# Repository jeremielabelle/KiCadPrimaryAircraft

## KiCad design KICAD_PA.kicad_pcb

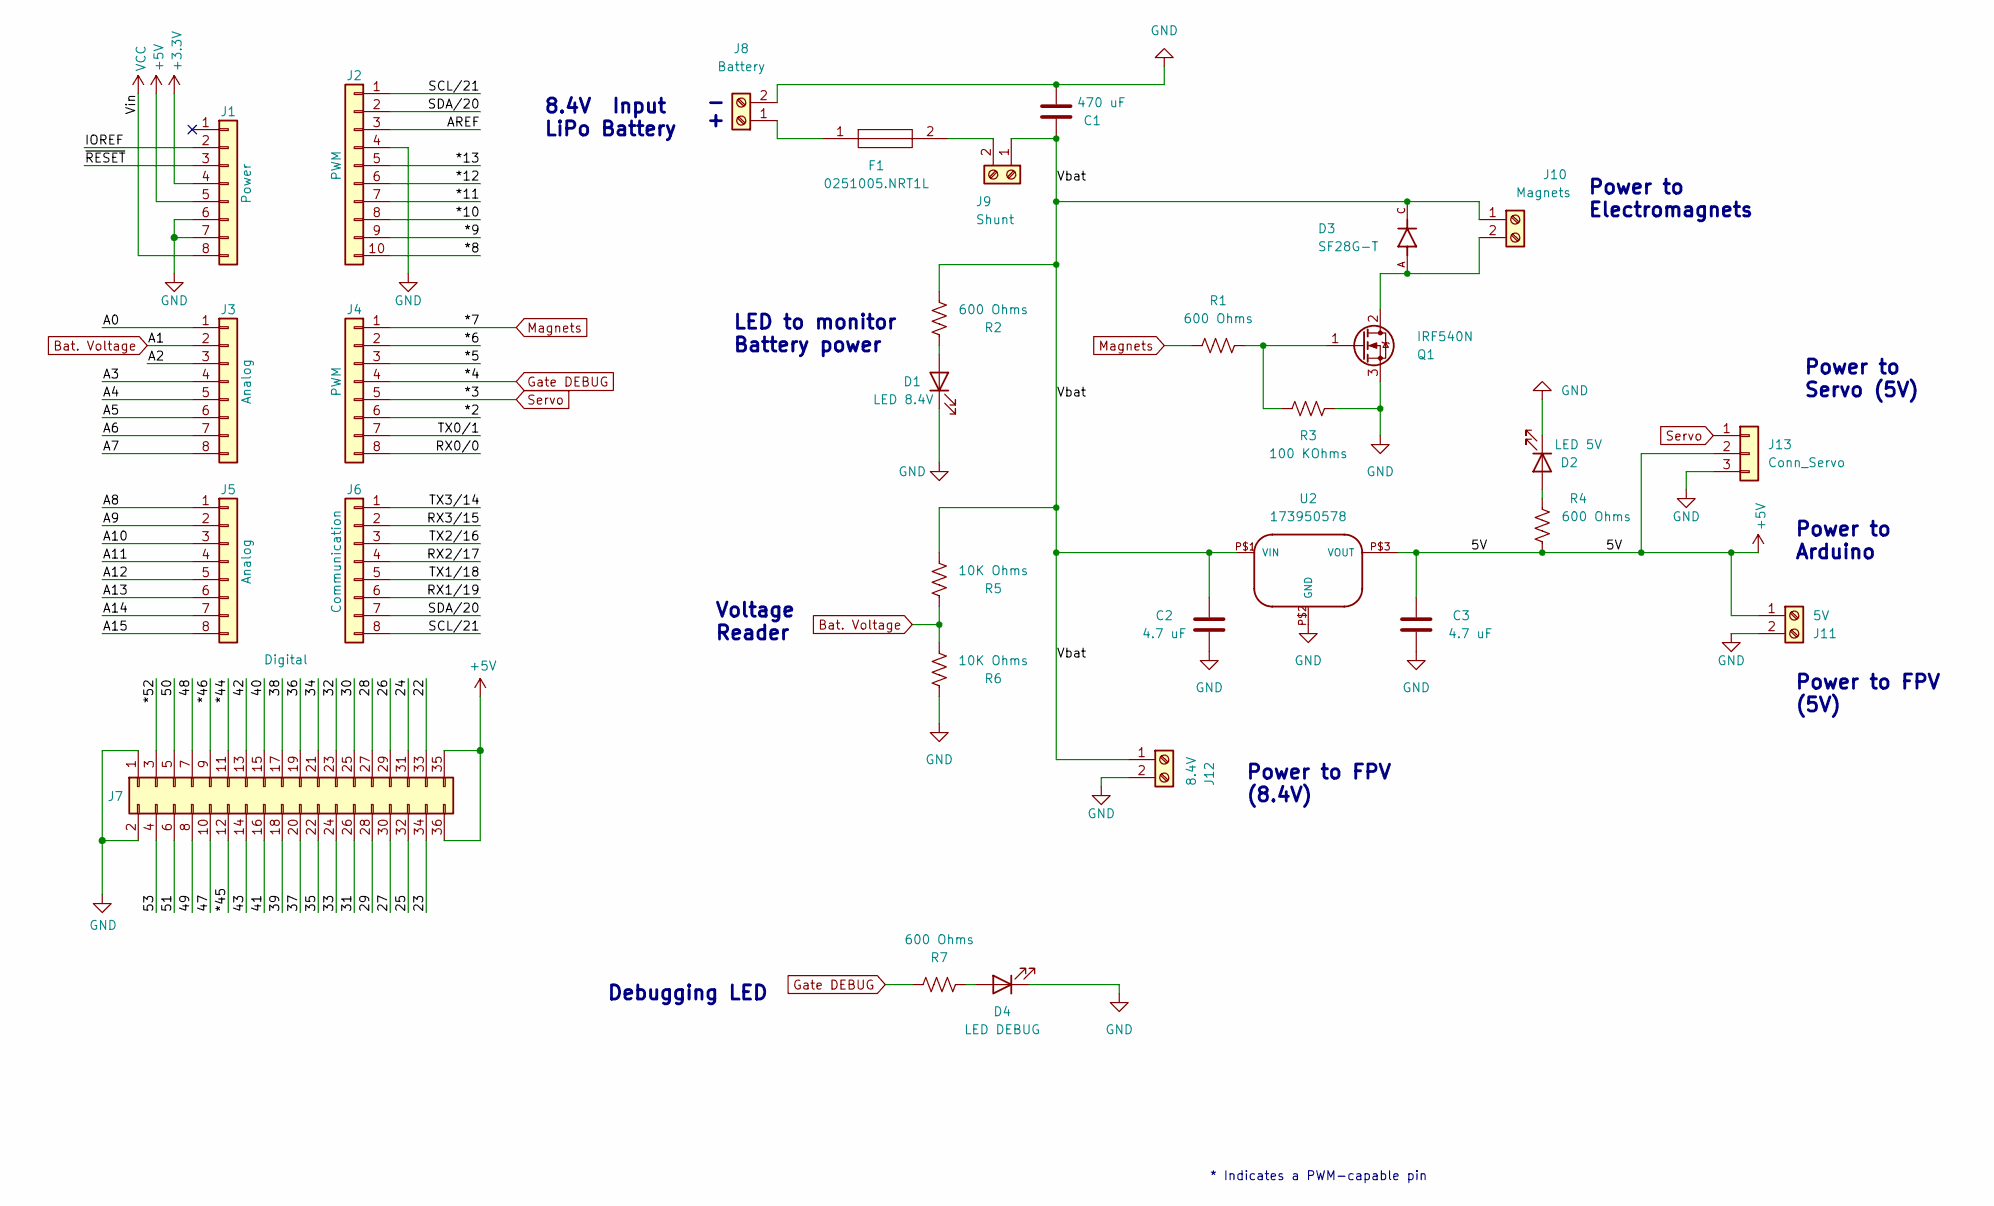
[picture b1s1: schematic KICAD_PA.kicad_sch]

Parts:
C1: 470 uF; CP_Radial_D12.5mm_P5.00mm
C2, C3: 4.7 uF; CP_Radial_D5.0mm_P2.00mm
D1: LED 8.4V; LED_D5.0mm_Horizontal_O3.81mm_Z3.0mm
D2: LED 5V; LED_D5.0mm_Horizontal_O3.81mm_Z3.0mm
D3: SF28G-T; DIOAD1300W80L670D310; PARTREV F2105
D4: LED DEBUG; LED_D5.0mm_Horizontal_O3.81mm_Z3.0mm
F1: 0251005.NRT1L; RESAD1831W64L711D280; Manufacturer_Part_Number 0251005.NRT1L; Mouser Part Number 576-0251005.NRT1L
J1: Power; PinSocket_1x08_P2.54mm_Vertical
J2: PWM; PinSocket_1x10_P2.54mm_Vertical
J3, J5: Analog; PinSocket_1x08_P2.54mm_Vertical
J4: PWM; PinSocket_1x08_P2.54mm_Vertical
J6: Communication; PinSocket_1x08_P2.54mm_Vertical
J7: Digital; PinSocket_2x18_P2.54mm_Vertical
J8: Battery; TerminalBlock_bornier-2_P5.08mm
J9: Shunt; TerminalBlock_bornier-2_P5.08mm
J10: Magnets; TerminalBlock_bornier-2_P5.08mm
J11: 5V; TerminalBlock_bornier-2_P5.08mm
J12: 8.4V; TerminalBlock_bornier-2_P5.08mm
J13: Conn_Servo; PinHeader_1x03_P2.54mm_Horizontal
Q1: IRF540N; TO-220-3_Vertical
R1, R2, R4, R7: 600 Ohms; R_Axial_DIN0207_L6.3mm_D2.5mm_P10.16mm_Horizontal
R3: 100 KOhms; R_Axial_DIN0516_L15.5mm_D5.0mm_P25.40mm_Horizontal
R5, R6: 10K Ohms; R_Axial_DIN0207_L6.3mm_D2.5mm_P10.16mm_Horizontal
U2: 173950578; SIP-3

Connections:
+3V3: J1.4
+5V: C3.1, J1.5, J7.35, J7.36, J11.1, J13.2, R4.2, U2.P$3 (VOUT)
/22: J7.33
/23: J7.34
/24: J7.31
/25: J7.32
/26: J7.29
/27: J7.30
/28: J7.27
/29: J7.28
/30: J7.25
/31: J7.26
/32: J7.23
/33: J7.24
/34: J7.21
/35: J7.22
/36: J7.19
/37: J7.20
/38: J7.17
/39: J7.18
/40: J7.15
/41: J7.16
/42: J7.13
/43: J7.14
/47: J7.10
/48: J7.7
/49: J7.8
/50: J7.5
/51: J7.6
/53: J7.4
/*2: J4.6
/*5: J4.3
/*6: J4.2
/*8: J2.10
/*9: J2.9
/*10: J2.8
/*11: J2.7
/*12: J2.6
/*13: J2.5
/*44: J7.11
/*45: J7.12
/*46: J7.9
/*52: J7.3
/A0: J3.1
/A2: J3.3
/A3: J3.4
/A4: J3.5
/A5: J3.6
/A6: J3.7
/A7: J3.8
/A8: J5.1
/A9: J5.2
/A10: J5.3
/A11: J5.4
/A12: J5.5
/A13: J5.6
/A14: J5.7
/A15: J5.8
/AREF: J2.3
/IOREF: J1.2
/RX0/0: J4.8
/RX1/19: J6.6
/RX2/17: J6.4
/RX3/15: J6.2
/SCL/21: J2.1, J6.8
/SDA/20: J2.2, J6.7
/TX0/1: J4.7
/TX1/18: J6.5
/TX2/16: J6.3
/TX3/14: J6.1
/Vbat: C1.1, C2.1, D3.C, J9.1, J10.1, J12.1, R2.2, R5.2, U2.P$1 (VIN)
/~RESET: J1.3
Bat. Voltage: J3.2, R5.1, R6.2
GND: C1.2, C2.2, C3.2, D1.1 (K), D2.1 (K), D4.1 (K), J1.6, J1.7, J2.4, J7.1, J7.2, J8.2, J11.2, J12.2, J13.3, Q1.3 (S), R3.1, R6.1, U2.P$2 (GND)
Gate DEBUG: J4.4, R7.2
Magnets: J4.1, R1.2
unnamed: D1.2 (A), R2.1
unnamed: D2.2 (A), R4.1
unnamed: D3.A, J10.2, Q1.2 (D)
unnamed: D4.2 (A), R7.1
unnamed: F1.1, J8.1
unnamed: F1.2, J9.2
unnamed: Q1.1 (G), R1.1, R3.2
Servo: J4.5, J13.1
VCC: J1.8

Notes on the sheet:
Power to Electromagnets
8.4V Input LiPo Battery
Power to Servo (5V)
Debugging LED
Power to Arduino
Power to FPV (8.4V)
Voltage Reader
* Indicates a PWM-capable pin
LED to monitor Battery power
Power to FPV (5V)

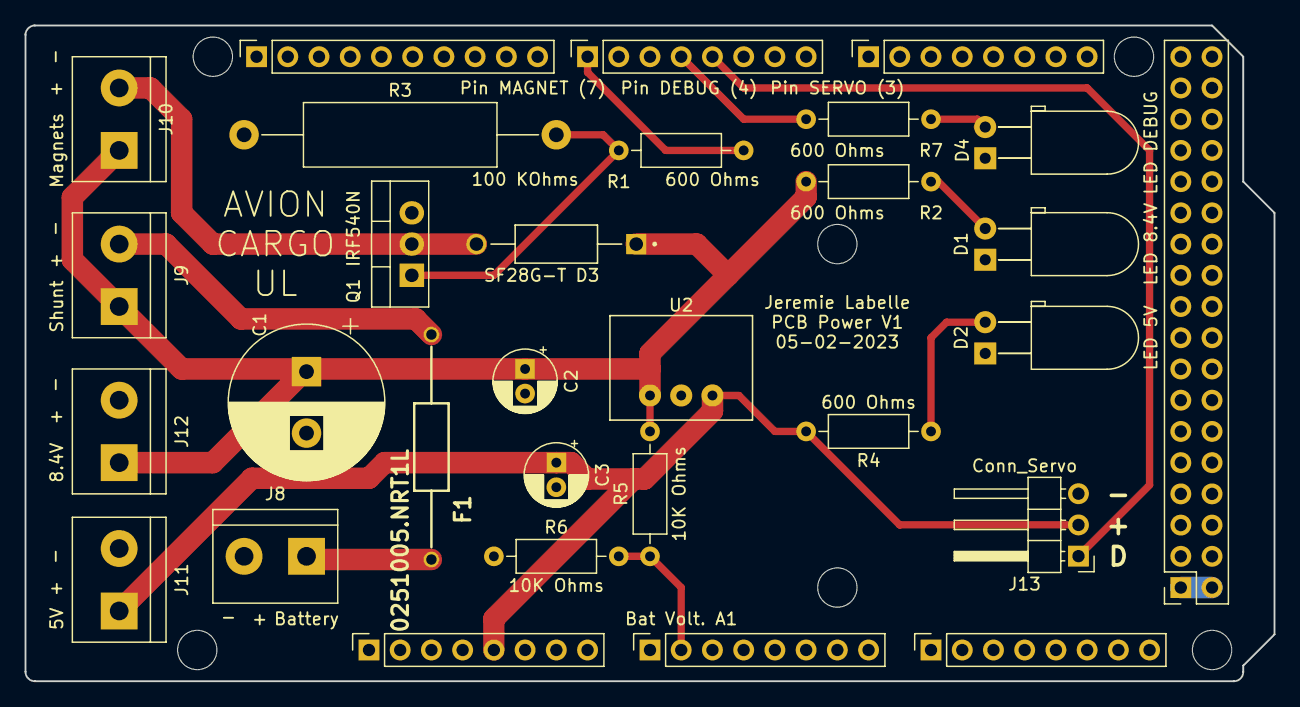
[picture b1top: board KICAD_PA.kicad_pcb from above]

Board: 2 copper layers, 101.6 x 53.3 mm, 36 parts (0 on the bottom side), 16 nets.

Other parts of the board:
MH1, MH2, MH3, MH4, MH5, MH6: MountingHole_3.2mm

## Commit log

2023-10-06 Initialisation du repo KiCAD
